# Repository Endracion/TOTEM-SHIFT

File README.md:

<picture align="center">
  <source media="(prefers-color-scheme: dark)" srcset="/docs/images/TOTEM_logo_dark.svg">
  <source media="(prefers-color-scheme: light)" srcset="/docs/images/TOTEM_logo_bright.svg">
  
</picture>

<h1 align="center">T O T E M - S H I F T</h1>

TOTEM-SHIFT is a modified 38 keys column-staggered split keyboard originally by GEIGEIGEIST.

This TOTEM-SHIFT version aims to allow for a larger battery and emphasize styling options through a swappable top plate held with magnets ([demo](https://www.youtube.com/watch?v=WX03MpgzbRs)). Meant to be used with a SEEED XIAO BLE (no longer supports the RP2040 with the TRRS port removed) for a wireless only build.

**WHY** a swappable top plate? Well I'm sure everyone has asked themselves at least once, which case should I go for? And then you're half locked into it.
I want to be able to change my mind, to change colors, logos, motifs or other surface effects to go with the style I want that day, so why not allow myself to do just that with a swappable top plate!

It was created for the SEEED XIAO keyboard contest by GEIGEIGEIST.\
[Here](https://www.hackster.io/geist/totem-a-tiny-splitkeyboard-with-splay-cb2e43) you can read about the process of making it.

Note that most of the guides and links will remain unchanged, the major changes will be to the 3D printed case design, as it uses the [TOTOEM Redux by VOID](https://www.printables.com/model/840146-totem-redux) case files as base, which are better suited to FDM 3D printing.

> **Note**
> The PCB is modified enought that this version will not be compatible with existing PCBs or cases for the original TOTEM.

***

## LAYOUT

***

## PCB

[Here](/PCB/TOTEM-SHIFT%200.4) you can find the KiCad files and Gerbers for the TOTEM.

Gerber files to upload for production are found [here](https://github.com/Endracion/TOTEM-SHIFT/tree/main/PCB/TOTEM-SHIFT%200.4/production).

***

## CASE

You can use the TOTEM without a case, but [here](https://www.printables.com/model/1033457-totem-shift-wireless-ble-redux-split-splay-keyboar) is the FDM 3D printed case I designed for it.

***

## BUILD GUIDE
  
The build guide for the TOTEM can be found [here](/docs/buildguide.md).

***

## FIRMWARE

[ZMK config](https://github.com/Endracion/zmk-config-totem-shift) for the TOTEM (wireless using the XIAO BLE)

The dongle version is coming at a later time.

***

## PHOTOS

This is the 3D printed TOTEM-SHIFT BLE Redux case with the MOTE keycaps.

This is the TOTEM in a black resin case

\
\

***

## BUY 

If there is enough interest, I may do a production run for this modified version, please feel free to reach out.

***

## CREDITS

### ORIGINAL CREATOR

The amazing [GEIGEIGEIST](https://github.com/GEIGEIGEIST) whose design are beautiful and inspiring.
VOID who created a FDM optimized case [TOTOEM Redux](https://www.printables.com/model/840146-totem-redux).
eiga for the [MOTE keycaps]{https://www.printables.com/model/864126-mote-choc-low-profile-flat-keycaps}.

### INSPIRATION

The additional pinky key makes the TOTEM compatible with the layout boards like the [Balbuzard](https://github.com/brow/balbuzard) by [Tom Brow](https://github.com/brow) and the [Osprette](https://github.com/smores56/osprette) by [Sam Mohr](https://github.com/smores56) use, where you put the keybinding of the top left and right keys on an outer pinky key.

### HELP FIXING THINGS

People who helped GEIGEIGEIST create this board and fix stuff:

#### PCB
- [Marco "Bob"](https://github.com/GroooveBob)

#### CASE
- [Freya](https://github.com/freya-irl)
- [Bubbleology](https://github.com/bubbleology)

#### FIRMWARE
- [Cem Aksoylar](https://github.com/caksoylar)
- [Grinnie](https://github.com/regicidalplutophage)
- [Alaa Saad Mansour](https://github.com/AlaaSaadAbdo)
- [pekudzu](https://github.com/pekudzu)

If you build a TOTEM, GEIGEIGEIST would be pretty happy to see some pictures. And if you want to leave him a tip you can do so [here](https://ko-fi.com/geigeigeist) (but please don't feel pressured)

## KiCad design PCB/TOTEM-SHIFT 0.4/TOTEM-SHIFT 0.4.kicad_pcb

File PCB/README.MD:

# TOTEM-SHIFT PCB FILES

I have modified the original PCB extensively, so here is a list of the largest changes:
- Moved the middle finger column down by approx 2.3mm, as it felt a little high compared to other boards.
- Made the underside of the XIAO easier to solder through a larger cutout.
- Moved the battery contact points above the diodes for the larger size battery cavity.
- Moved the diodes to the rear to make a little more space for the battery and for a clean top PCB.
- Rerouted many traces, cleaned up others and added many diagonal angles for aesthetic purposes and to remove acute angles which are more prone to manufacturing errors.
- Removed the TRRS connector completely as this is a wireless-centric design now.
- Replaced the reset and power switches with hidden ones inside of the top plate, where the TRRS used to be. This gives the case a completely clean look.
- Removed the large color silkscreens as while they were super nice, it was not possible for me to edit them in a way that looked good since I don't have the source files.
- Moved a few other things to make place for these changes.
- Tried to realign one of the holes on the right as it wasn't mirrored properly.
- Everything has been updatd for KiCad 8.0 and gerber files should be able to be easily uploaded to PCB manufacturer websites, I've provided my gerber zip file prepared by JLCPCB's plugin.

> **Note**
> As a reminder: The PCB is modified enought that this version will not be compatible with existing PCBs or cases for the original TOTEM.

# TOTEM-SHIFT FUTURE

What I'm thinking of working on next after this build is complete and I'm satisfied using it.

- [ ] Utilize additional pins from NFC/Sense for ?
- [ ] Implement support for LCD on the board or on the dongle (for layer visibility and style)
- [ ] Implement support for encoder
- [ ] Implement support for pointing device (touchpad, trackpad, mini trackball)
- [ ] Recreate a similar board from scratch that's fully reversible

# TOTEM PCB FILES

## MANUFACTURING
If you want to get the PCB made you need to download the [ZIP](/PCB/totem_0-3/totem_0-3_gerbers.zip/) and upload it to the website of the manufacture 
I can recommend [JLCPCB](https://jlcpcb.com/), [Seeed Fusion](https://www.seeedstudio.com/fusion_pcb.html) or [PCBway](https://www.pcbway.com/).

- Download [the ZIP file](/PCB/TOTEM-SHIFT%200.4/production/TOTEM-SHIFT_split_keyboard_0.4.zip)
- Upload the ZIP file to the website of the manufacturer.
- Sometimes the Gerber preview from JLCPCB can't display the PCB, even when the files are fine. In this case use these dimensions: 258.7mm * 94.35mm.
- PCB Thickness: 1.6mm
- Layers: 2
- Different designs: 2 (because both halves are not the same).
- PCB Qty as much as you like, but minimum is always 5. One PCB is a full keyboard.
- PCB Color Black (or any other color you like).
- No impedance control.
- Surface Finish HASL (with lead) if you want the easiest soldering experience or LeadFree HASL.
- Remove Order Number: Yes

***

## CHECK PINOUT OR TRACES

If you only want to check the traces or see what is connected to which pin you can take a look at these graphics.
You can also take a look at the [schematics](TOTEM_0-3_schematics.pdf) and the [PCB](TOTEM_0-3_PCB.pdf) as PDF.

***

***

## TAKE A DEEPER LOOK OR MODIFY 

You can download the project if you need to take a deeper look or modify something. You need the Open Source software [KiCad](https://www.kicad.org/) to open it.

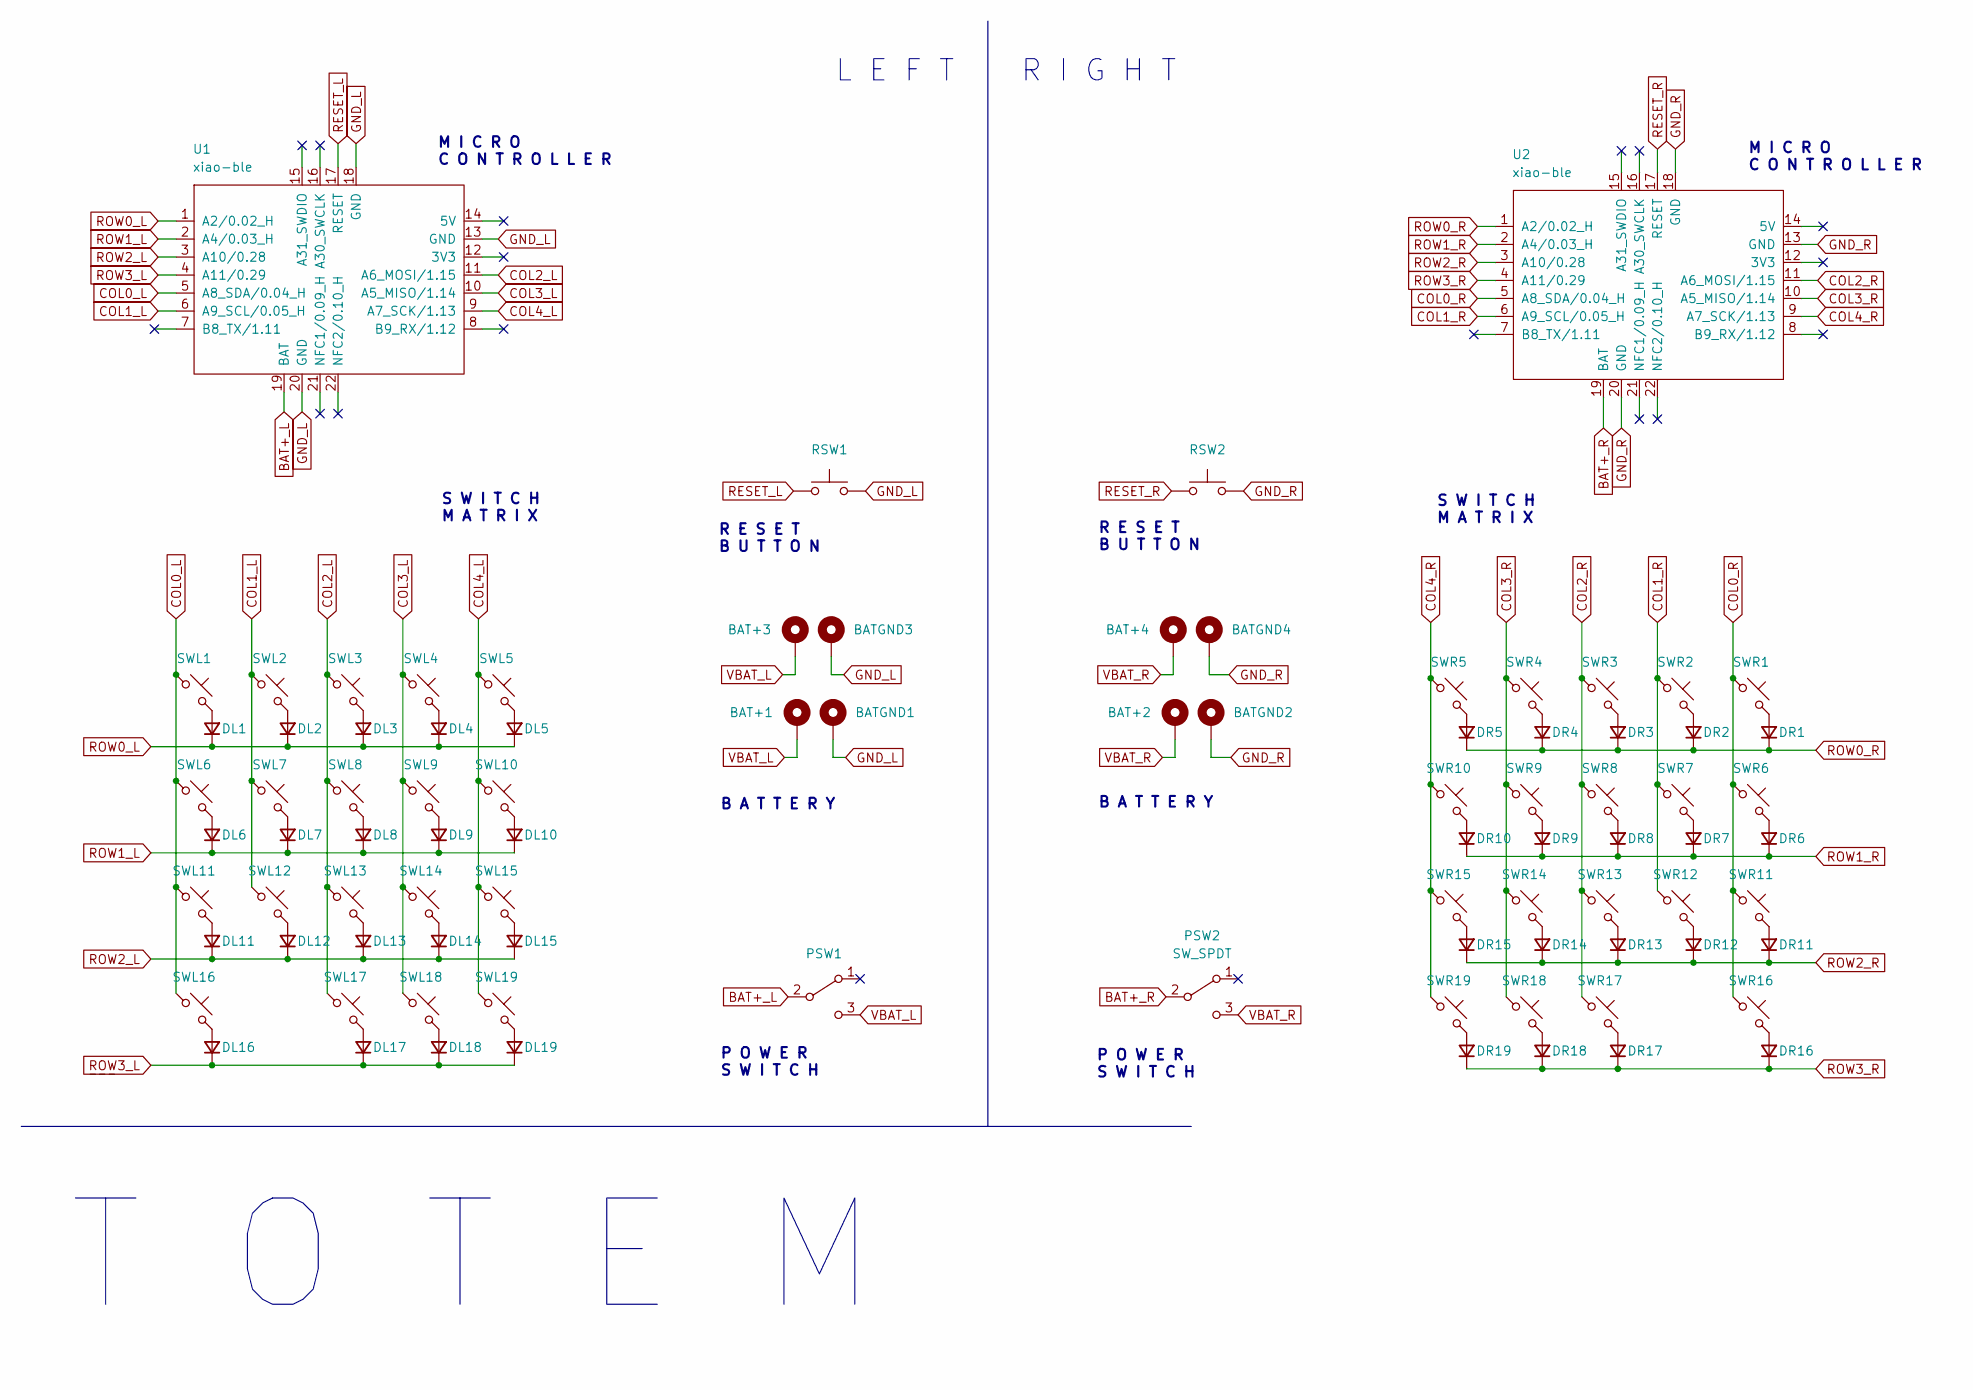
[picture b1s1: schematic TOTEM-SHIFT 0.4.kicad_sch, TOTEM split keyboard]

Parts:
BAT+1, BAT+2, BAT+3, BAT+4: +; BatteryPad
BATGND1, BATGND2, BATGND3, BATGND4: -; BatteryPad
DL1, DL2, DL3, DL4, DL5, DL6, DL7, DL8, DL9, DL10, DL11, DL12, DL13, DL14, DL15, DL16, DL17, DL18, DL19: D_Small; Diode_SOD123
DR1, DR2, DR3, DR4, DR5, DR6, DR7, DR8, DR9, DR10, DR11, DR12, DR13, DR14, DR15, DR16, DR17, DR18, DR19: D_Small; Diode_SOD123
PSW1, PSW2: SW_SPDT; MSK12C02
RSW1, RSW2: SW_Push; SW_PUSH_1P1T_6x3.5mm_H5.0_APEM_MJTP1250
SWL1, SWL2, SWL3, SWL4, SWL5, SWL6, SWL7, SWL8, SWL9, SWL10, SWL11, SWL12, SWL13, SWL14, SWL15, SWL16, SWL17, SWL18, SWL19: SW_Push_45deg; Kailh_socket_PG1350_optional
SWR1, SWR2, SWR3, SWR4, SWR5, SWR6, SWR7, SWR8, SWR9, SWR10, SWR11, SWR12, SWR13, SWR14, SWR15, SWR16, SWR17, SWR18, SWR19: SW_Push_45deg; Kailh_socket_PG1350_optional
U1, U2: xiao-ble; xiao-ble-smd-cutout

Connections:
BAT+_L: PSW1.2 (B), U1.19 (BAT); also elsewhere on the board
BAT+_R: PSW2.2 (B), U2.19 (BAT); also elsewhere on the board
COL0_L: SWL1.1, SWL6.1, SWL11.1, SWL16.1, U1.5 (A8_SDA/0.04_H)
COL0_R: SWR1.1, SWR6.1, SWR11.1, SWR16.1, U2.5 (A8_SDA/0.04_H)
COL1_L: SWL2.1, SWL7.1, SWL12.1, U1.6 (A9_SCL/0.05_H)
COL1_R: SWR2.1, SWR7.1, SWR12.1, U2.6 (A9_SCL/0.05_H)
COL2_L: SWL3.1, SWL8.1, SWL13.1, SWL17.1, U1.11 (A6_MOSI/1.15)
COL2_R: SWR3.1, SWR8.1, SWR13.1, SWR17.1, U2.11 (A6_MOSI/1.15)
COL3_L: SWL4.1, SWL9.1, SWL14.1, SWL18.1, U1.10 (A5_MISO/1.14)
COL3_R: SWR4.1, SWR9.1, SWR14.1, SWR18.1, U2.10 (A5_MISO/1.14)
COL4_L: SWL5.1, SWL10.1, SWL15.1, SWL19.1, U1.9 (A7_SCK/1.13)
COL4_R: SWR5.1, SWR10.1, SWR15.1, SWR19.1, U2.9 (A7_SCK/1.13)
GND_L: BATGND1.1, BATGND3.1, RSW1.2, U1.13 (GND), U1.18 (GND), U1.20 (GND); also elsewhere on the board
GND_R: BATGND2.1, BATGND4.1, RSW2.2, U2.13 (GND), U2.18 (GND), U2.20 (GND); also elsewhere on the board
unnamed: DL1.2 (A), SWL1.2
unnamed: DL2.2 (A), SWL2.2
unnamed: DL3.2 (A), SWL3.2
unnamed: DL4.2 (A), SWL4.2
unnamed: DL5.2 (A), SWL5.2
unnamed: DL6.2 (A), SWL6.2
unnamed: DL7.2 (A), SWL7.2
unnamed: DL8.2 (A), SWL8.2
unnamed: DL9.2 (A), SWL9.2
unnamed: DL10.2 (A), SWL10.2
unnamed: DL11.2 (A), SWL11.2
unnamed: DL12.2 (A), SWL12.2
unnamed: DL13.2 (A), SWL13.2
unnamed: DL14.2 (A), SWL14.2
unnamed: DL15.2 (A), SWL15.2
unnamed: DL16.2 (A), SWL16.2
unnamed: DL17.2 (A), SWL17.2
unnamed: DL18.2 (A), SWL18.2
unnamed: DL19.2 (A), SWL19.2
unnamed: DR1.2 (A), SWR1.2
unnamed: DR2.2 (A), SWR2.2
unnamed: DR3.2 (A), SWR3.2
unnamed: DR4.2 (A), SWR4.2
unnamed: DR5.2 (A), SWR5.2
unnamed: DR6.2 (A), SWR6.2
unnamed: DR7.2 (A), SWR7.2
unnamed: DR8.2 (A), SWR8.2
unnamed: DR9.2 (A), SWR9.2
unnamed: DR10.2 (A), SWR10.2
unnamed: DR11.2 (A), SWR11.2
unnamed: DR12.2 (A), SWR12.2
unnamed: DR13.2 (A), SWR13.2
unnamed: DR14.2 (A), SWR14.2
unnamed: DR15.2 (A), SWR15.2
unnamed: DR16.2 (A), SWR16.2
unnamed: DR17.2 (A), SWR17.2
unnamed: DR18.2 (A), SWR18.2
unnamed: DR19.2 (A), SWR19.2
RESET_L: RSW1.1, U1.17 (RESET); also elsewhere on the board
RESET_R: RSW2.1, U2.17 (RESET); also elsewhere on the board
ROW0_L: DL1.1 (K), DL2.1 (K), DL3.1 (K), DL4.1 (K), DL5.1 (K), U1.1 (A2/0.02_H)
ROW0_R: DR1.1 (K), DR2.1 (K), DR3.1 (K), DR4.1 (K), DR5.1 (K), U2.1 (A2/0.02_H)
ROW1_L: DL6.1 (K), DL7.1 (K), DL8.1 (K), DL9.1 (K), DL10.1 (K), U1.2 (A4/0.03_H)
ROW1_R: DR6.1 (K), DR7.1 (K), DR8.1 (K), DR9.1 (K), DR10.1 (K), U2.2 (A4/0.03_H)
ROW2_L: DL11.1 (K), DL12.1 (K), DL13.1 (K), DL14.1 (K), DL15.1 (K), U1.3 (A10/0.28)
ROW2_R: DR11.1 (K), DR12.1 (K), DR13.1 (K), DR14.1 (K), DR15.1 (K), U2.3 (A10/0.28)
ROW3_L: DL16.1 (K), DL17.1 (K), DL18.1 (K), DL19.1 (K), U1.4 (A11/0.29)
ROW3_R: DR16.1 (K), DR17.1 (K), DR18.1 (K), DR19.1 (K), U2.4 (A11/0.29)
VBAT_L: BAT+1.1, BAT+3.1, PSW1.3 (C); also elsewhere on the board
VBAT_R: BAT+2.1, BAT+4.1, PSW2.3 (C); also elsewhere on the board
VCC_L: U1.12 (3V3)
VCC_R: U2.12 (3V3)

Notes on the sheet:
M I C R O C O N T R O L L E R
R E S E T B U T T O N
S W I T C H M A T R I X
P O W E R S W I T C H
T O T E M
B A T T E R Y
R I G H T
L E F T

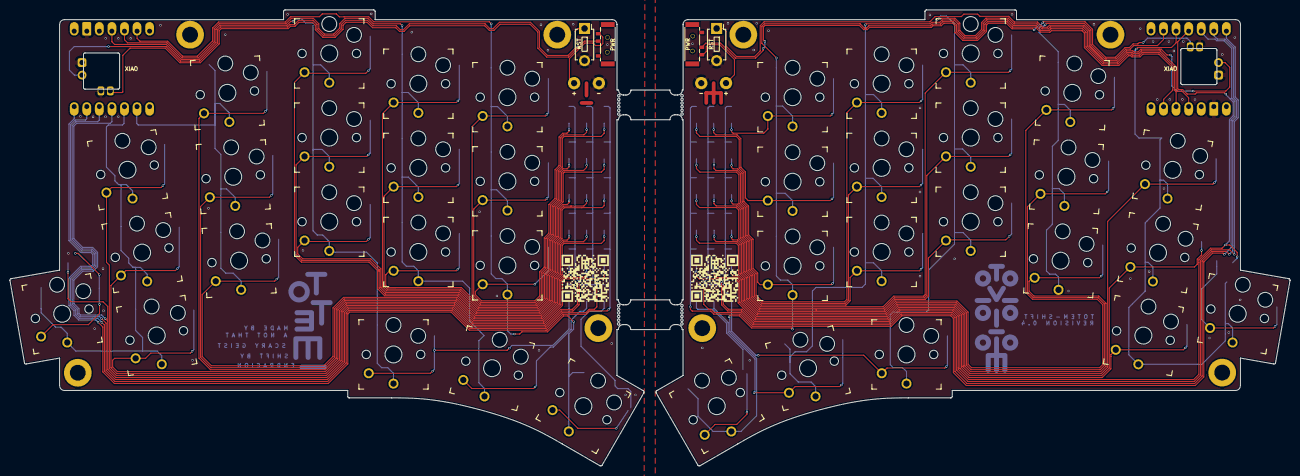
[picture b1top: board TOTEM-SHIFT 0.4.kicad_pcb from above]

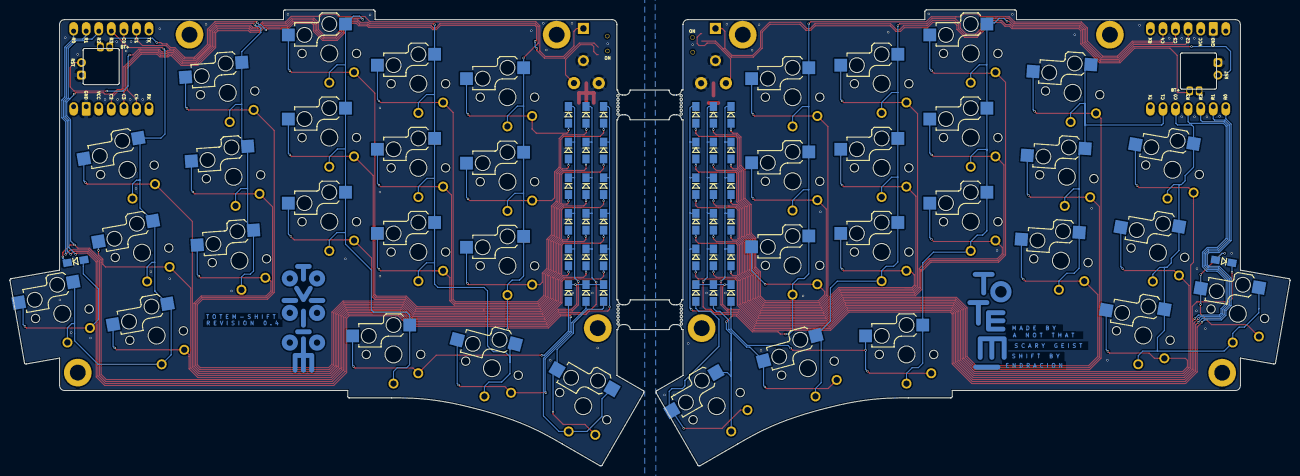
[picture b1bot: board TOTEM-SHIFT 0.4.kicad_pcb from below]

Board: 2 copper layers, 258.7 x 92.2 mm, 86 parts (38 on the bottom side), 64 nets.

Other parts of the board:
PWR: SW_SPDT; MSK12C02
PWR#2: SW_SPDT; MSK12C02
RST: SW_Push; SW_PUSH_1P1T_6x3.5mm_H5.0_APEM_MJTP1250
RST#2: SW_Push; SW_PUSH_1P1T_6x3.5mm_H5.0_APEM_MJTP1250

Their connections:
BAT+_L: PWR.2 (B); also elsewhere on the board
BAT+_R: PWR#2.2 (B); also elsewhere on the board
GND_L: RST.2; also elsewhere on the board
GND_R: RST#2.2; also elsewhere on the board
RESET_L: RST.1; also elsewhere on the board
RESET_R: RST#2.1; also elsewhere on the board
VBAT_L: PWR.3 (C); also elsewhere on the board
VBAT_R: PWR#2.3 (C); also elsewhere on the board

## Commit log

2024-08-19 Update README.md
    Clarified differences with original TOTEM.
2024-08-19 Update README.md
    Typos
2024-08-19 Update README.md
    More readme changes.
2024-08-26 v0.4 Modifications
2024-08-26 Added TOTEM-SHIFT Redux STLs
2024-08-26 Added TOTEM-SHIFT Redux Readme
2024-08-26 Corrected main readme
2024-08-26 Corrected case readme
2024-08-26 Update PCB readme
2024-09-02 Testing Hidden Power Switch
2024-09-02 Small PCB trace fixes
2024-09-04 Major changes, hidden switches and case redesign
2024-09-04 Readme updates
2024-10-08 PCB ready for production update
2024-10-08 Reorganized readmes and case
2024-10-08 Build guide updates
2024-10-08 v8 Case
